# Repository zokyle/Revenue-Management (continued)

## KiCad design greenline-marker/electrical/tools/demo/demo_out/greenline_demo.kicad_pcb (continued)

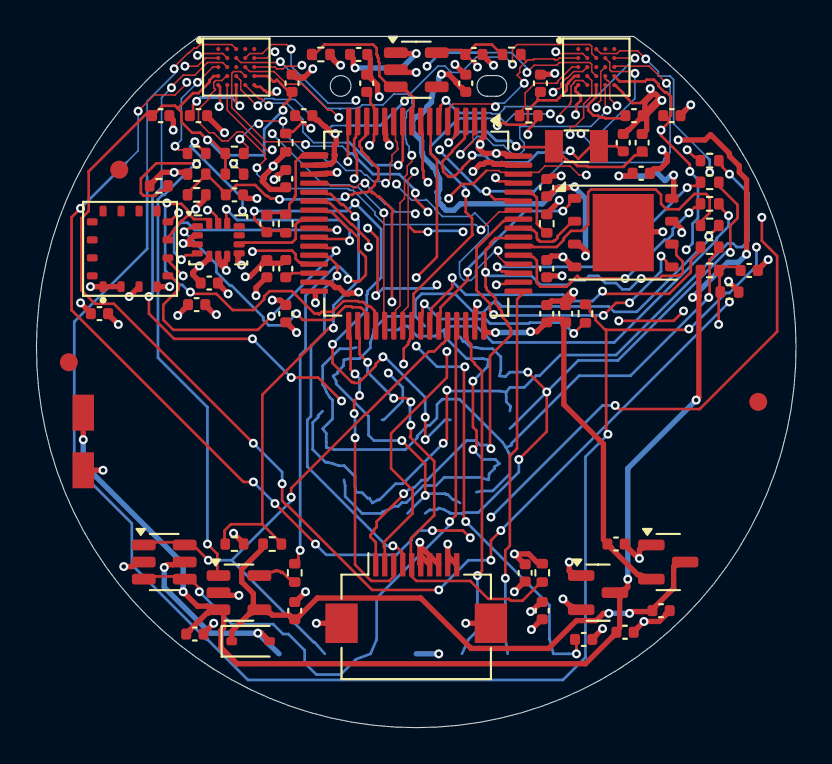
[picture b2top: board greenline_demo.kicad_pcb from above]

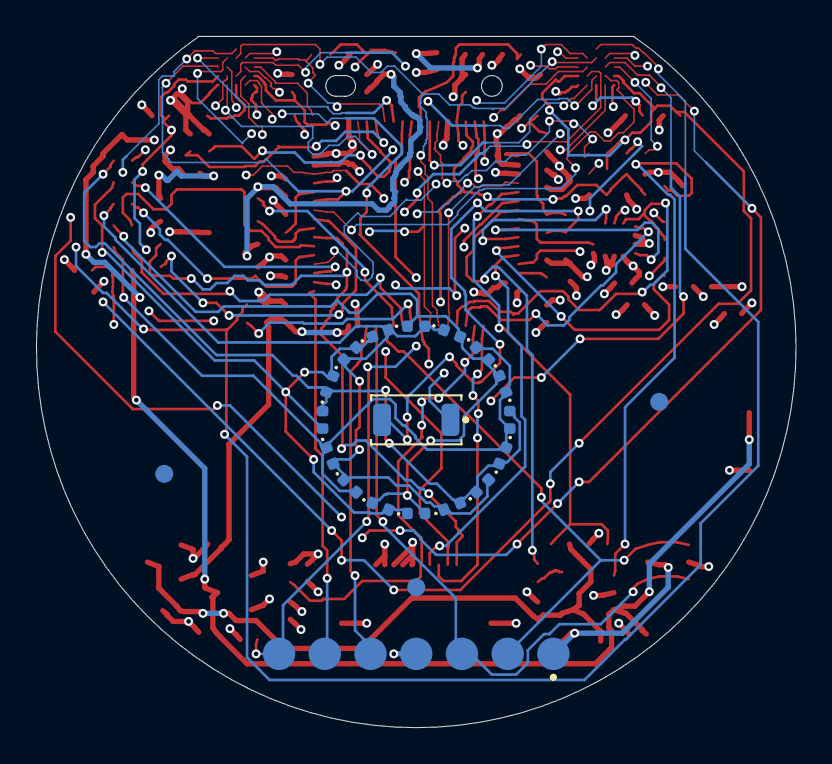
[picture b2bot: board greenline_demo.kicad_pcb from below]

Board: 4 copper layers, 42.2 x 38.4 mm, 101 parts (21 on the bottom side), 72 nets.

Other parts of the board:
FID1, FID2, FID3, FID4, FID5, FID6: Fiducial; Fiducial_1mm_Mask2mm
H1: NPTH 1.15mm; NPTH_1.15mm

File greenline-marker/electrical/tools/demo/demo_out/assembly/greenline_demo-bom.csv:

Item,Qty,References,Value,Description,Footprint,MPN,Manufacturer,Distributor,Distributor PN,Unit Price,Extended Price,DNP
1,17,C1 C2 C4 C5 C7 C10 C13 C14 C17 C18 C21 C22 C23 C24 C25 C27 C35,100n,MLCC 0402 100n,Capacitor_SMD:C_0402_1005Metric,GRM155R71C104KA88D,Murata,Digi-Key,490-3261-1-ND,0.0200,0.3400,
2,4,C3 C6 C29 C30,4u7,MLCC 0402 4u7,Capacitor_SMD:C_0402_1005Metric,GRM155R60J475ME47D,Murata,Digi-Key,490-5915-1-ND,0.0600,0.2400,
3,11,C8 C15 C16 C19 C20 C28 C31 C32 C33 C34 C36,1u,MLCC 0402 1u,Capacitor_SMD:C_0402_1005Metric,GRM155R61A105KE15D,Murata,Digi-Key,490-3890-1-ND,0.0300,0.3300,
4,1,C9,10n,MLCC 0402 10n,Capacitor_SMD:C_0402_1005Metric,GRM155R71H103KA88D,Murata,Digi-Key,490-1312-1-ND,0.0200,0.0200,
5,2,C11 C12,6p8,MLCC 0402 6p8,Capacitor_SMD:C_0402_1005Metric,GRM1555C1H6R8CA01D,Murata,Digi-Key,490-5947-1-ND,0.0300,0.0600,
6,1,C26,10p,MLCC 0402 10p,Capacitor_SMD:C_0402_1005Metric,GRM1555C1H100JA01D,Murata,Digi-Key,490-5921-1-ND,0.0300,0.0300,
7,8,D1 D3 D5 D7 D9 D11 D13 D15,LED red,grain LED 0402,LED_SMD:LED_0402_1005Metric,APHHS1005SURCK,Kingbright,Digi-Key,754-1104-1-ND,0.3500,2.8000,
8,8,D2 D4 D6 D8 D10 D12 D14 D16,LED NIR,grain LED 0402,LED_SMD:LED_0402_1005Metric,APHHS1005F3C,Kingbright,Digi-Key,754-1105-1-ND,0.3500,2.8000,
9,1,D17,Schottky,VBUS series Schottky,Diode_SMD:D_SOD-323,BAT60JFILM,STMicroelectronics,Digi-Key,497-3707-1-ND,0.3000,0.3000,
10,1,J1,LCD FPC 10,"LCD FPC connector, 10 x 0.5 mm",Connector_FFC-FPC:Hirose_FH12-10S-0.5SH_1x10-1MP_P0.50mm_Horizontal,FH12A-10S-0.5SH(55),Hirose,Digi-Key,HFJ110CT-ND,0.9000,0.9000,
11,1,PD1,Photodiode,photodiode (stand-in land pattern),gleda:Photodiode_4.8x2.5mm,VEMD5510C,Vishay,Digi-Key,VEMD5510CCT-ND,1.2000,1.2000,
12,5,R1 R2 R3 R4 R5,68R,Resistor 0402 1% 68R,Resistor_SMD:R_0402_1005Metric,RC0402FR-0768RL,Yageo,Digi-Key,RC0402FR-0768RL-ND,0.0100,0.0500,
13,1,R6,10R,Resistor 0402 1% 10R,Resistor_SMD:R_0402_1005Metric,RC0402FR-0710RL,Yageo,Digi-Key,RC0402FR-0710RL-ND,0.0100,0.0100,
14,1,R7,10k,Resistor 0402 1% 10k,Resistor_SMD:R_0402_1005Metric,RC0402FR-0710KL,Yageo,Digi-Key,RC0402FR-0710KL-ND,0.0100,0.0100,
15,3,R8 R9 R12,2k2,Resistor 0402 1% 2k2,Resistor_SMD:R_0402_1005Metric,RC0402FR-072K2L,Yageo,Digi-Key,RC0402FR-072K2L-ND,0.0100,0.0300,
16,3,R10 R11 R13,33R,Resistor 0402 1% 33R,Resistor_SMD:R_0402_1005Metric,RC0402FR-0733RL,Yageo,Digi-Key,RC0402FR-0733RL-ND,0.0100,0.0300,
17,7,R14 R17 R18 R19 R21 R22 R25,100k,Resistor 0402 1% 100k,Resistor_SMD:R_0402_1005Metric,RC0402FR-07100KL,Yageo,Digi-Key,RC0402FR-07100KL-ND,0.0100,0.0700,
18,1,R16,470k,Resistor 0402 1% 470k,Resistor_SMD:R_0402_1005Metric,RC0402FR-07470KL,Yageo,Digi-Key,RC0402FR-07470KL-ND,0.0100,0.0100,
19,1,R20,49k9,Resistor 0402 1% 49k9,Resistor_SMD:R_0402_1005Metric,RC0402FR-0749K9L,Yageo,Digi-Key,RC0402FR-0749K9L-ND,0.0100,0.0100,
20,2,R23 R24,1M,Resistor 0402 1% 1M,Resistor_SMD:R_0402_1005Metric,RC0402FR-071ML,Yageo,Digi-Key,RC0402FR-071ML-ND,0.0100,0.0200,
21,1,U1,STM32U585RIT6,"MCU, LQFP-64",Package_QFP:LQFP-64_10x10mm_P0.5mm,STM32U585RIT6,STMicroelectronics,Digi-Key,497-STM32U585RIT6-ND,9.5000,9.5000,
22,2,U2 U3,OVM7692,camera cube (stand-in ball map),gleda:CamCube_BGA25_P0.5,OVM7692-RYAA,OmniVision,Digi-Key,884-1027-1-ND,6.0000,12.0000,
23,1,U4,LSM6DSV16X,"6-axis IMU, LGA-14",Package_LGA:LGA-14_3x2.5mm_P0.5mm_LayoutBorder3x4y,LSM6DSV16XTR,STMicroelectronics,Digi-Key,497-LSM6DSV16XTRCT-ND,4.5000,4.5000,
24,1,U5,Inclinometer,"inclinometer, LGA-16 (stand-in pin map)",gleda:LGA-16_5x5mm_P1.0mm,IIS2ICLXTR,STMicroelectronics,Digi-Key,497-IIS2ICLXTRCT-ND,18.0000,18.0000,
25,1,U6,SPI flash,"SPI NOR flash 64 Mbit, WSON-8 6x5",Package_SON:WSON-8-1EP_6x5mm_P1.27mm_EP3.4x4.3mm,MX25R6435FZNIL0,Macronix,Digi-Key,1092-1187-1-ND,1.6000,1.6000,
26,1,U7,MCP1700-2.8,"LDO 2.8 V, always on",Package_TO_SOT_SMD:SOT-23,MCP1700T-2802E/TT,Microchip,Digi-Key,MCP1700T2802ETTCT-ND,0.4500,0.4500,
27,1,U8,LP5907-2.8,LDO 2.8 V for the cameras,Package_TO_SOT_SMD:SOT-23-5,LP5907MFX-2.8/NOPB,Texas Instruments,Digi-Key,296-38557-1-ND,0.6000,0.6000,
28,1,U9,MCP73831,Li-Po charger,Package_TO_SOT_SMD:SOT-23-5,MCP73831T-2ACI/OT,Microchip,Digi-Key,MCP73831T-2ACI/OTCT-ND,0.7000,0.7000,
29,1,U10,USBLC6-2SC6,USB ESD protection,Package_TO_SOT_SMD:SOT-23-6,USBLC6-2SC6,STMicroelectronics,Digi-Key,497-5235-1-ND,0.4000,0.4000,
30,1,U11,MCP1700-3.3,LDO 3.3 V for VDDUSB,Package_TO_SOT_SMD:SOT-23,MCP1700T-3302E/TT,Microchip,Digi-Key,MCP1700T3302ETTCT-ND,0.4500,0.4500,
31,1,Y1,32.768k,32.768 kHz crystal 3215,Crystal:Crystal_SMD_3215-2Pin_3.2x1.5mm,ABS07-120-32.768KHZ-T,Abracon,Digi-Key,535-11937-1-ND,0.6000,0.6000,

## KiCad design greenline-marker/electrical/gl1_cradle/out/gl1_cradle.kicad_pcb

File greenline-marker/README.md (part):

# GreenLine GL-1

Overview of the design package at revision E-EVT1 (revision E of the design, prepared for the first engineering test build; the words are explained below). Written 2026-11-20 for the owner of the project.

## 1. What this is, in five sentences

GreenLine GL-1 is the design of an electronic golf ball marker: a D-shaped puck 46.0 mm across and 7.6 mm thick that is set down behind the ball on a putting green.
It measures the direction and distance to the flagstick with two very small cameras, the tilt of the ground under it with an inertial sensor, and (as an experiment that ships switched off) the lean of the grass with a ring of small lights.
From those measurements it computes where to start the putt and draws that line on a round display on its top face, with the distance, the slope and the expected break.
It has no radio and no buttons; it is driven by placing, tapping and turning it, and it charges and exchanges data in a small cradle with a USB-C socket.
It is a practice and training device, and everything in this directory is a design on paper: no unit exists.

### Words used in this file

| Word | Meaning here |
|---|---|
| Revision E, E-EVT1 | The current issue of the design; the files also mention the earlier revisions C and D. EVT stands for engineering validation test: the first hand-built units, made to find out what is wrong. E-EVT1 is revision E as prepared for the first such build. |
| Specification | `design/DESIGN_SPEC.md`, the file that states what the product is and every design decision. |
| Amendment | A numbered change to the specification. Revision E has 36 of them, E1 to E36. |
| PROVISIONAL | The package's own mark for a value that was written down from memory or from a search extract and is not confirmed against the maker's document. |
| PROPOSED | A requirement or limit that is stated and that nobody has adopted or measured. |
| NOT MET | A requirement that the firmware model does not meet. A model result, not a measurement. |
| Gate | A question that must have a written answer before money is spent on something that cannot be undone. |
| Data sheet | The manufacturer's own document for a part. |
| Pin table, ball map | The table that says which pin of a chip carries which signal. Very small chips have solder balls underneath instead of pins; their table is called a ball map. |
| Stand-in | A plausible value or table put in so that the design could go on. It is not the maker's. |
| Routed board | A circuit board whose wiring (its copper tracks) has been drawn in full, so that fabrication files exist. "Changing the copper" means changing that wiring. |
| Design-rule check | An automatic check that the tracks of a board keep the widths and gaps the fabricator needs. |
| Firmware | The program that runs on the marker's processor. |
| Linked image | The one file that can be loaded into the processor. The firmware has been compiled (each source file checked and translated) but never linked into that file. |
| USB loader | A program that the processor's maker builds into the chip for loading new firmware over USB. |
| mrad | Milliradian: a slope or angle of 1 mm per metre, or 0.1 %. |

## 2. Status: read this before anything else

> **This is a design package. Nothing has been built.**
>
> - The package was produced entirely by software agents. No circuit board, printed part, fixture or marker has been fabricated, assembled, measured or run. The firmware has only ever run on a PC simulator.
> - No supplier has been asked for a quote and nothing has been ordered, certified or approved.
> - Every performance figure in this file is the output of a model or a simulation. None is a measurement.
> - [docs/RELEASE_GATES.md](docs/RELEASE_GATES.md) lists **104 open gates** between this package and the four orders that lead to a product (boards, enclosure and parts, building test units, selling). 32 of them are decisions that only the owner can take.
> - Several pin tables and part dimensions were written down from memory or from search extracts. The package marks them PROVISIONAL. The automatic checks compare the design with itself; they cannot tell whether a pin table copied from memory is the real one.

The request was for a "fully US-sourceable and ready to manufacture device". The package is not at that stage. The table says what "ready" covers today and what it does not.

| "Ready" does mean | "Ready" does not mean |
|---|---|
| The design is complete enough to review: specification, parameters, 3D models and drawings, two routed circuit boards with fabrication files, firmware that passes its tests on a PC, a simulation, and plans for sourcing, building and testing. | That boards or parts can be ordered today. 43 gates stand before the first board order alone. |
| The automatic checks of the package pass: the mechanical check report shows all checks passing, with 23 warnings and 8 recorded deviations from the specification, and the design-rule check of both boards shows 0 errors (`mechanical/export/check_report.md`; `electrical/README.md`, "Result"). | That the parts of the design agree with each other everywhere. The checks cover only what they compare. Known disagreements that no check covers: the cradle spring pin is drawn with a 0.635 mm tail in a 0.80 mm hole on the board and with a 0.76 mm tail in a 0.90 mm hole in the mechanical model (gate G-014); the files disagree on whether the two statement blocks of the legend hold 88 characters each or 88 together (G-045); `mechanical/README.md` gives the depth of the cradle pilot holes as 3 mm in one place and 3.2 mm in three others (G-107). Nor do the checks show that the design agrees with the real parts: that is what the PROVISIONAL items are about. |
| 64 of the 86 lines of the sourcing list are marked VERIFIED: 55 of the 72 purchased lines were seen listed by a US distributor or seller (42 with a stock figure), and for 9 of the 14 custom parts and outside services a US company was seen advertising that kind of work. No quote has been requested, and 17 purchased lines cannot be bought as they stand (`docs/SOURCING.md` sections 1.1 and 1.4). | That the device is US-made or "US-sourced". Where each part is made is unknown for almost every line, and the compliance checklist advises against the phrase in public (gates G-093 and G-097). |
| There is a written list of what must happen next, in order. | That the device works. Whether it reads a putt as well as the simulation says depends on inputs nobody has measured (section 6). |

The name for this stage is an EVT design package. EVT stands for engineering validation test: the first hand-built units, made to find out what is wrong.

This is a kitchen drawn on paper where the position of the sink was sketched from memory (the picture is from `docs/RELEASE_GATES.md`). The drawing is complete and consistent with itself, but the worktop must not be cut until someone has measured the real sink.

## 3. What it looks like

All six pictures are computer renders of the 3D model. Each carries the note "PROVISIONAL - not released" in its footer. They are not photographs.

*The assembled marker from the front and above. The flat face in front is the "visor", which points at the hole; the two small rectangles in it are the camera windows. The round glass on top covers the display, which is seen through a 22 mm opening. The small cross on the left of the top face is the vent with its drain grooves.*

*The underside. The plate is circuit-board material with a printed legend; the words "MAKER NAME" and "STATEMENTS RESERVED" are placeholders, because the regulatory text is not decided (gate G-085). The ring in the middle is the grain sensor: pairs of small lights round a light detector, sealed under clear resin. The slot at the bottom shows seven gold contact pads. The user's cradle touches four of them with spring pins (power, two data lines, ground); the other three are for the factory. The three small dots are steel or ceramic balls that stand 0.10 mm proud and act as feet on a hard surface.*

*Exploded view, with the labels of the render. The main parts, from top to bottom: cover glass, tape ring, the printed shell ("Tub"), the display ("Memory LCD"), a foam pad (the grey-purple rectangle), the battery ("LiPo cell"), the two camera cubes with their small fold prisms, the main circuit board ("Main PCB assembly"), an adhesive sheet, the baffle ring of the grain sensor (a black ring that keeps stray light from the light detector), and the base plate with its three ball feet. The small parts between them: two visor windows with their adhesive frames, the vent, two black hood gaskets, the adhesive frame and the flexible tail of the display, the battery leads, the black tape annulus under the baffle ring, the perimeter seal, the clear potting of the grain opening and the potting of the three balls. The round purple disc, second from the top, is an optional trial film (amendment E9) that is meant to keep the display readable through polarised sunglasses.*

*Cut-away. The stack at the centre, from the bottom: base plate, adhesive, circuit board, battery, foam, display glass, cover glass. On the right, one camera: the camera cube sits flat on the board and looks straight up, and a 2 mm prism on top of it turns its view forward through the visor window.*

*The marker in its charging and data cradle, seen from the rear right. The marker fits one way round only. A fixed lip holds its front edge and a sprung latch with a thumb tab holds the rear. The USB-C socket is in the rear face of the cradle.*

*Section through the marker in its cradle. A spring pin in the cradle presses up against a contact pad on the marker's underside; the lip and the latch hold the marker down against the pins. The floor of the cradle is drained.*

## 4. How it works

Each part is explained first with an everyday picture and then with the real mechanism and its numbers. Unless another file is named, the numbers come from `design/DESIGN_SPEC.md` (sections 2 to 6).

### 4.1 Two cameras: two eyes judging distance

**The picture.** Hold a finger at arm's length and look at it with one eye, then the other. The finger appears to jump sideways against the background. The closer the finger, the bigger the jump. Your brain uses that jump to judge distance. The marker does the same with two cameras a fixed distance apart, looking at the flagstick.

**The mechanism.**

- Two OmniVision OVM7692 camera cubes (each 2.95 x 3.47 x 2.76 mm) sit 20.0 mm apart. That spacing is the "baseline". The jump between the two images is called disparity and is measured in pixels. The focal length of the lens, expressed in pixels, is 657: an object 657 times as far away as it is wide covers one pixel.
- The cameras look out 5.6 mm above the turf. From that height the green is seen almost edge-on, so the cameras **cannot** map the surface between ball and hole: everything beyond a couple of metres collapses into one or two pixel rows. The specification says this plainly. What the cameras do deliver is the flagstick.
- From the flagstick they take three things: the direction to the hole (expected quality about 1 milliradian, which is 1 mm sideways per metre of distance), the distance, and the height of the lowest visible point of the stick, which tells whether the hole is above or below the ball.
- Two eyes 20 mm apart judge far distances poorly. For long putts the marker also uses the apparent height of the flagstick, which it learns per course. The simulated error of the combined distance (random part only) is 1 % at 1.5 m, 2 % at 3 m, 3.4 % at 6 m and 5 % at 12 m. The stick's top is only in view beyond about 6.6 m on a nominal unit and about 8.4 m on a worst-case one.
- The flagstick must be in the hole. Without it the golfer points the marker at the hole and dials in the distance, and the result is marked as approximate.
- PROVISIONAL: the pattern of solder balls under the camera and the lens data behind the field-of-view figures are not confirmed against the maker's documents. The camera pattern is the gravest single gate (G-001): if it is wrong, both camera areas of the board are redone.

### 4.2 The inertial sensor: a carpenter's level

**The picture.** A carpenter's level shows which way a surface tips by where the bubble goes. The marker carries an electronic version of that bubble. Lying on the green, it reads which way the ground under it falls and how steeply.

**The mechanism.**

- The part is an ST LSM6DSV16X, an inertial sensor that measures acceleration (and so the direction of gravity) and rotation. The firmware averages gravity for 1 second once the marker has lain still for 0.5 second.
- The sensor itself is expected to be good to about 0.5 milliradian. A milliradian (mrad) is a slope of 1 mm per metre, or 0.1 %.
- The weak point is not the sensor but how the puck sits on grass: the estimate is 2 to 5 mrad of error per placement, and **nobody has measured it**. The specification calls seating "the dominant error of the whole instrument". The simulation shows the tilt reading does nearly all the work for the aim line, so this unmeasured number decides how good the device is.
- A carpenter checks a level by turning it end for end. The marker uses the same trick twice: the Precision Read (read, spin the marker 180 degrees in place, read again) cancels the device's own bias, and the user zeroing routine on a hard flat surface works the same way.
- One reading tells the slope under the ball only. The slope along the rest of the putt can differ. Survey mode exists for that: two to four placements along the line.

### 4.3 The grain sensor: stroking velvet, with light

**The picture.** Stroke velvet one way and it looks light; stroke it the other way and it looks dark, because the fibres lean. Grass on a green leans too ("grain"), and a ball rolls differently with and against it. The grain sensor does not touch the grass. It shines small lights on it from different sides in turn and watches which side looks brightest.

**The mechanism.**

- On the underside, 16 small LEDs sit on a ring of 5.2 mm radius round one light detector (a photodiode): eight red and eight near-infrared, arranged as eight pairs at eight positions round the ring, 45 degrees apart (`design/master_params.yaml`, `grain_led_ring`). So the grass is lit from eight directions in two colours, which makes 16 separate lights.
- Each LED is switched on in turn and the detector reading is compared with the reading with the LED off. The research note's model puts the brightest direction on the side the blades lean away from (`docs/research/grain-sensing.md`).
- **This is the least proven part of the design.** The specification's own entry reads: "Unproven. Reviewer estimate 15-25 % chance the optical reading improves the line." The research note found that for a single reading the random noise is as large as the signal.
- For that reason the grain sensor ships disabled, and every accuracy figure in section 6 is without it.

### 4.4 The solver: rolling a virtual ball until it drops

**The picture.** Imagine a practice green inside the marker that matches what it just measured. The marker rolls a virtual ball on it, sees where the ball ends up, corrects the aim and the speed, and rolls again, until the ball goes through the hole at the wanted pace. The aim of that last roll is the line it draws.

**The mechanism.**

- From the tilt and the height of the hole the firmware fits a simple curved surface between ball and hole. The sources call it a "quadratic patch": a surface that can tilt and bend like a shallow dish or saddle, and cannot ripple. It then needs the green speed, which the golfer enters as a Stimp number (the usual measure of how fast a green is).
- The ball's motion is computed in small time steps: friction slows it, slope pulls it sideways. The target pace is a ball that would stop 0.30 m past the hole on a flat green (adjustable).
- It takes few rolls and many small steps. In the firmware's own bench table a typical Quick Read takes 5 trial rolls and about 730 time steps; over 240 simulated reads the most was 57 rolls and 25,144 steps (`firmware/README.md`, section "Solver"). The work is capped at 300,000 steps, about 1 to 2 seconds by the timing model.
- On very steep slopes no stable answer exists: near the slope on which a ball no longer stops, the review found the aim flipping on a one-microradian change of input. The marker then says "TOO STEEP" and draws only a dashed line, or no line (amendments E31 and E33).
- The firmware solver is a C port of the Python reference in `sim/`, and is tested against it on a PC.

### 4.5 The electronics as a block diagram

```mermaid
flowchart LR
    subgraph CRADLE["Cradle"]
        USBC["USB-C socket, 5 V"]
        PINS["4 spring pins in the user cradle (of 7 pads): power, 2 data, ground"]
        USBC --> PINS
    end

    subgraph POWER["Power"]
        SW["Ideal-diode switch"]
        CHG["Charger BQ25101, 19.8 mA"]
        CELL["Lithium-polymer cell, about 43 mAh listed"]
        REG["2.8 V regulator, always on"]
        CAMREG["2.8 V camera regulator, on only during a read"]
        SW --> CHG --> CELL
        CELL --> REG
        CELL --> CAMREG
    end

    subgraph BRAIN["Processor"]
        MCU["STM32U585 microcontroller"]
    end

    subgraph SENSE["Sensors"]
        CAML["Camera left"]
        CAMR["Camera right"]
        IMU["Inertial sensor: tilt, taps, turns"]
        GRAIN["Grain ring: 16 LEDs and 1 photodiode"]
    end

    DISP["Display, 128 x 128 points"]
    FLASH["Memory chip: settings, calibration, log"]

    PINS -->|"5 V"| SW
    PINS <-->|"USB data"| MCU
    REG --> MCU
    CAMREG --> CAML
    CAMREG --> CAMR
    CAML -->|"shared image bus"| MCU
    CAMR -->|"shared image bus"| MCU
    IMU <--> MCU
    GRAIN <--> MCU
    MCU --> DISP
    MCU <--> FLASH
```

What to notice in the diagram: power flows from the cradle on the left through the charger into the cell, and from the cell through two regulators to everything else; every sensor reports to the one processor; nothing leaves the marker except through the cradle pins.

Three terms in the boxes. The ideal-diode switch is an electronic one-way valve: it lets the cradle's 5 V in and lets nothing flow back out to the contact pads. A regulator turns the cell's changing voltage into a steady 2.8 V. The shared image bus is one set of data lines that both cameras use in turn, so the processor reads one camera at a time.

Points worth knowing, all from `design/DESIGN_SPEC.md` sections 3 and 4:

- There is one processor and no radio. Settings are made on the device; logs, calibration and firmware updates go through the cradle as an ordinary USB device.
- The cameras are powered only during a read, because they take most of the energy (92 % of the charge of a read in the model, `docs/POWER_BUDGET.md`).
- The charger has its own temperature sensor at the cell and stops charging outside its temperature window without any help from the firmware. Its temperature thresholds and its pin table are PROVISIONAL.
- The marker has seven contact pads. The user's cradle fits four spring pins. The factory version of the cradle fits all seven; the three extra pins give service access to the processor.

### 4.6 One read, step by step

```mermaid
sequenceDiagram
    participant G as Golfer
    participant M as Marker (processor)
    participant I as Inertial sensor
    participant C as Two cameras
    participant D as Display

    G->>M: Place the marker behind the ball, visor toward the hole
    I->>M: Motion wakes the marker
    I->>M: Still for 0.5 s (settle)
    I->>M: Gravity averaged for 1 s (tilt)
    M->>C: Camera power on
    C->>M: Image strips, left right right left, repeated
    M->>C: Camera power off after 2.2 to 2.8 s
    M->>M: Find the flagstick, combine the two distance estimates, fit the surface, solve the putt
    M->>D: Draw the line, distance, slope, break, confidence
    D->>G: Result 4.15 to 4.84 s after the marker came to rest
    Note over M,D: The result stays for 45 s, then the marker sleeps
```

The times are from the firmware's timing model in the current test log (`firmware/build/readme/test.log`): 4.45 s at the nominal setting, 4.15 to 4.84 s over the estimated range. Amendment E15 of the specification still says "4.1 to 4.8 s", from an earlier run of the model. The times are not measured, and the model rests on an estimated factor between PC and processor speed (gate G-077).

## 5. Key numbers

| Item | Value | Standing | Source |
|---|---|---|---|
| Marker size | 46.0 mm across, 7.6 mm thick, D-shaped | Design value | `design/DESIGN_SPEC.md` section 1 |
| Marker mass | 12.11 g | Estimate from the 3D model with typical densities, no solder | `mechanical/README.md` section 2 |
| Cradle | 60 x 60 mm, 22.6 mm high overall; about 30.4 g for the factory version with all seven pins (the user cradle has four) | Design value; mass estimated | `design/DESIGN_SPEC.md` section 5; `mechanical/README.md` section 2 |
| Cell | Lithium-polymer, 2 x 10 x 30 mm, about 43 mAh. With its protection board it is modelled as 34 x 10 x 2 mm, which is the size on the label in the exploded view | Listing only; capacity, protection-board length (PROVISIONAL) and safety certificates not obtained. The research notes suspect 34 mAh | `design/DESIGN_SPEC.md` section 3; `mechanical/README.md` part list item 4; `docs/POWER_BUDGET.md` section 1 |
| Charging | 19.8 mA in the cradle; at least 2.2 h from empty | Model; no model of a whole charge exists | `docs/POWER_BUDGET.md` section 2 |
| Read time | Result 4.15 to 4.84 s after the marker comes to rest (4.45 s nominal); cameras on for 2.16 to 2.76 s | MODEL, not measured. The specification (E15) still says 4.1 to 4.8 s | `firmware/build/readme/test.log`; `firmware/README.md` "End to end" |
| Reads per charge | 594 read cycles to empty (528 to 658) | MODEL on the listed capacity | `docs/POWER_BUDGET.md` section 3 |
| Standby | 76 days asleep to empty, underside dark (23.68 microamps) | MODEL | `docs/POWER_BUDGET.md` sections 2 and 3 |
| Ship mode (the lowest power state, for the weeks in a box) | 12.93 microamps against a requirement of at most 5 | **NOT MET** in the model; needs a hardware change or a changed requirement. The specification and the YAML still say ship mode is not modelled (gate G-107) | `docs/POWER_BUDGET.md` section 4 |
| Display | Sharp memory LCD, 128 x 128 points, seen through a 22 mm round opening | Part chosen; tail geometry and pin order PROVISIONAL | `design/DESIGN_SPEC.md` sections 3 and 4 |
| Cameras | Two, 20.0 mm apart, focal length 657 pixels, optical axis 5.6 mm above the turf | Design values; ball pattern and lens data PROVISIONAL | `design/DESIGN_SPEC.md` sections 2 and 5 |
| Main board | 4 layers, 0.8 mm thick, D-shaped | Routed; design-rule check passes; not ordered | `design/DESIGN_SPEC.md` section 4; `electrical/README.md` |
| Cradle board | 2 layers, 1.0 mm thick | Routed; not ordered | `design/DESIGN_SPEC.md` E36 |
| Open gates | 104 (43 + 20 + 22 + 19), of them 32 owner decisions | Count on 2026-11-20, after three gates closed and five were added that day | `docs/RELEASE_GATES.md` sections 1 and 10 |

## 6. How accurate would it be? What the simulation says, and what it does not

The package contains a simulation (`sim/`). It builds synthetic greens on a computer, simulates what the marker's sensors would report on them, runs the same estimator the firmware uses, and then rolls the ball along the line the marker would show. Doing this for many random cases is called a Monte Carlo run.

**What the run covers** (`sim/results/REPORT.md`): 3600 putts, at six lengths from 1.5 to 12 m, on four classes of synthetic green, 150 greens per class and length. Seating error of the puck assumed 2.5 mrad. Grain sensor off. The table below is for a perfect stroke along the displayed line, all lengths pooled.

| Method | Putts holed | Holed at 3 m | Holed at 6 m | Median sideways miss |
|---|---|---|---|---|
| No read: aim straight at the flag | 8.9 % | 11 % | 4 % | 23.2 cm |
| Quick Read (one placement) | 29.5 % | 44 % | 13 % | 9.9 cm |
| Precision Read (read, spin, read) | 31.6 % | 48 % | 14 % | 8.6 cm |
| Survey, three placements | 34.4 % | 52 % | 23 % | 7.1 cm |
| A golfer who reads cross slope to 0.5 % | 29.5 % | 42 % | 14 % | 9.5 cm |
| A golfer who reads cross slope to 1 % | 19.3 % | 25 % | 7 % | 16.4 cm |

Source: `sim/results/REPORT.md` section 1.

In words: in the simulation a Quick Read is about level with a golfer who reads slope very well, and clearly ahead of one who reads it moderately well. With human stroke error added (1 degree in direction, 6 % in speed, which the report calls an elite level) the Quick Read holes 21.0 % and even a perfect read holes only 32.7 %.

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
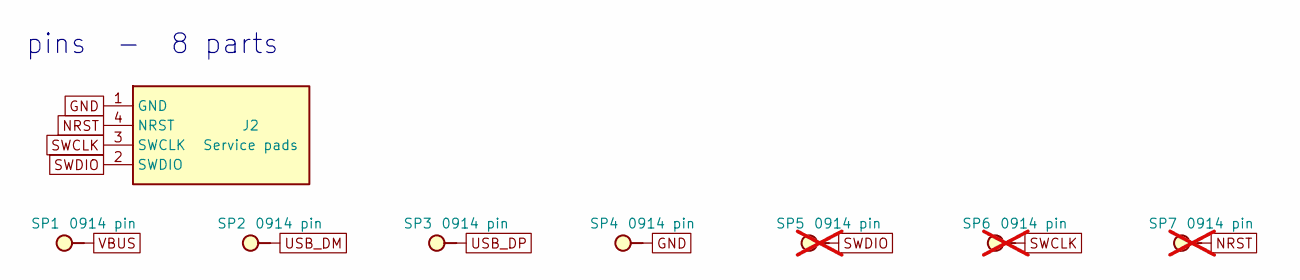
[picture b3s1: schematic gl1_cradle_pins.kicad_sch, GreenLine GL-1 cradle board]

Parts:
J2: Service pads; ServicePads_4x1.5mm_P2.54
SP1, SP2, SP3, SP4: 0914 pin; MillMax_0914_TH_PROVISIONAL; MPN 0914-0-15-20-77-14-11-0
SP5, SP6, SP7: 0914 pin; MillMax_0914_TH_PROVISIONAL; MPN 0914-0-15-20-77-14-11-0; not fitted

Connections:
GND: J2.1 (GND), SP4.1; also elsewhere on the board
NRST: J2.4 (NRST), SP7.1
SWCLK: J2.3 (SWCLK), SP6.1
SWDIO: J2.2 (SWDIO), SP5.1
USB_DM: SP2.1; also elsewhere on the board
USB_DP: SP3.1; also elsewhere on the board
VBUS: SP1.1; also elsewhere on the board

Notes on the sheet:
pins - 8 parts

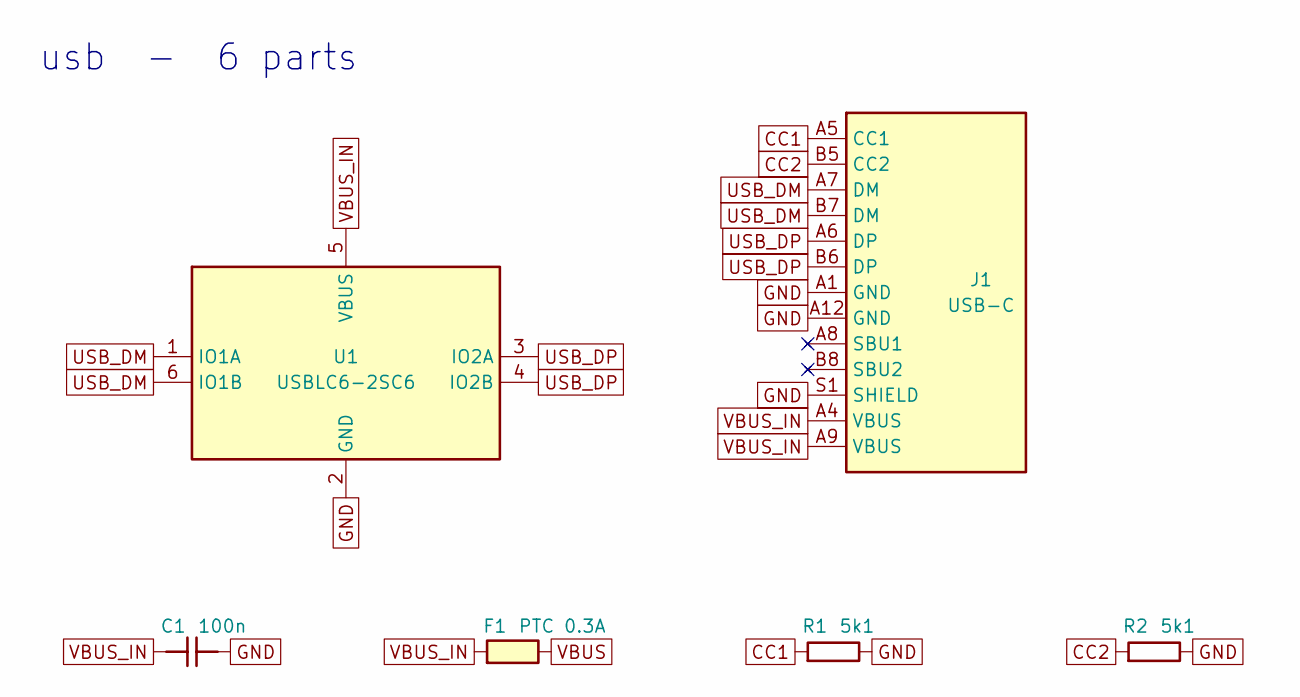
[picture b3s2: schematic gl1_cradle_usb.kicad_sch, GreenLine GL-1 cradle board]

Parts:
C1: 100n; C_0402_1005Metric; MPN GRM155R71C104KA88D
F1: PTC 0.3A; Fuse_0603_1608Metric; MPN MF-FSMF035X-2
J1: USB-C; USB_C_Receptacle_GCT_USB4105-xx-A_16P_TopMnt_Horizontal_GL1; MPN USB4105-GF-A
R1, R2: 5k1; R_0402_1005Metric; MPN RC0402FR-075K1L
U1: USBLC6-2SC6; SOT-23-6; MPN USBLC6-2SC6

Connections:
CC1: J1.A5 (CC1), R1.1
CC2: J1.B5 (CC2), R2.1
GND: C1.2, J1.A1 (GND), J1.A12 (GND), J1.S1 (SHIELD), R1.2, R2.2, U1.2 (GND); also elsewhere on the board
USB_DM: J1.A7 (DM), J1.B7 (DM), U1.1 (IO1A), U1.6 (IO1B); also elsewhere on the board
USB_DP: J1.A6 (DP), J1.B6 (DP), U1.3 (IO2A), U1.4 (IO2B); also elsewhere on the board
VBUS: F1.2; also elsewhere on the board
VBUS_IN: C1.1, F1.1, J1.A4 (VBUS), J1.A9 (VBUS), U1.5 (VBUS)

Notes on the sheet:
usb - 6 parts

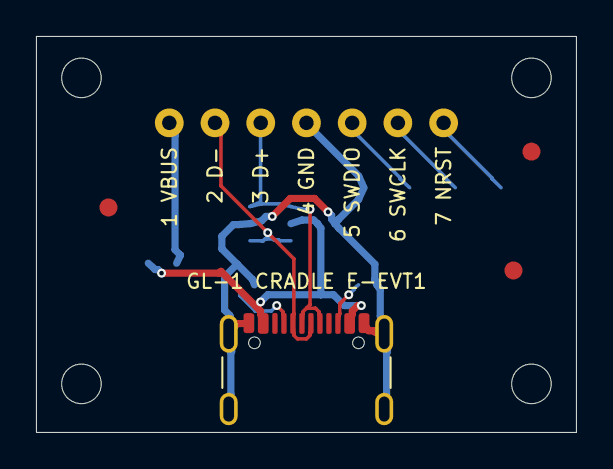
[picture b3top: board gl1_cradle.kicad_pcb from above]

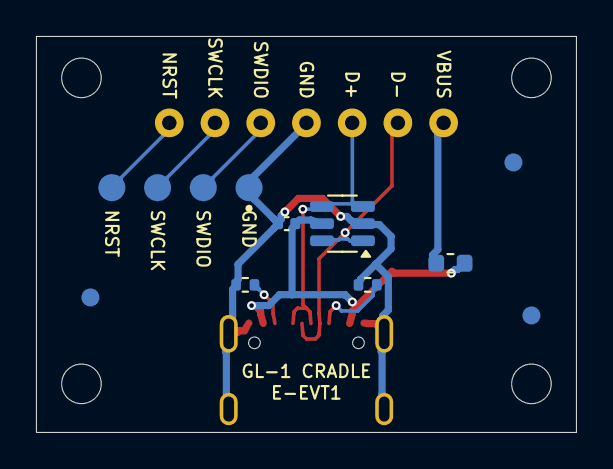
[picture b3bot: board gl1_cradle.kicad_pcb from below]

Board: 2 copper layers, 30.0 x 22.0 mm, 24 parts (9 on the bottom side), 10 nets.

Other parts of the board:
FID1, FID2, FID3, FID4, FID5, FID6: Fiducial; Fiducial_1mm_Mask2mm
MH1, MH2, MH3, MH4: NPTH 2.2mm; NPTH_2.2mm

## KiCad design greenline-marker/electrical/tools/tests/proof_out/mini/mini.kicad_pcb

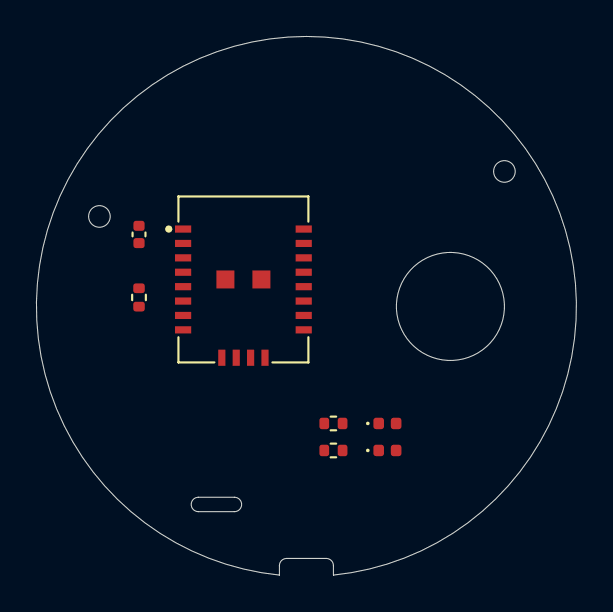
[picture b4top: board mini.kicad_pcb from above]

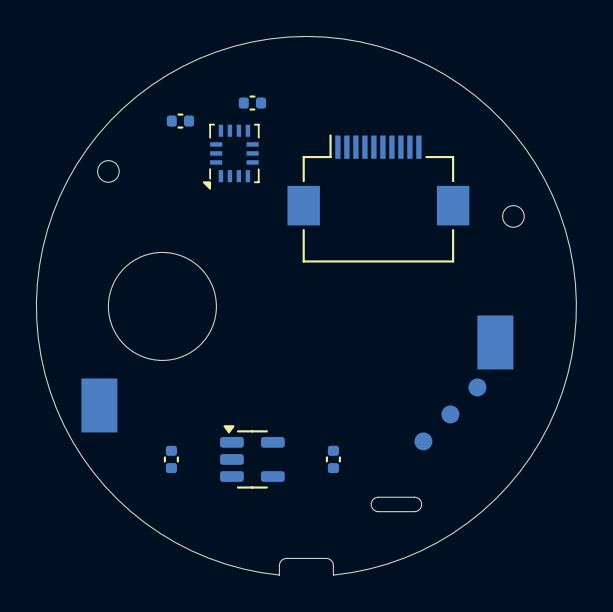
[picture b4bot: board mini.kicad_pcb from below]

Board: 4 copper layers, 30.0 x 29.9 mm, 21 parts (12 on the bottom side), 19 nets, no tracks yet.

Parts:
BT1: BAT+; BatteryTab_2x3mm
BT2: BAT-; BatteryTab_2x3mm
C1, C3, C4: 1u; C_0402_1005Metric
C2, C5: 100n; C_0402_1005Metric
D1, D2: LED; LED_0402_1005Metric
H1, H2: NPTH 1.2mm; NPTH_1.2mm
J1: FPC 10; Hirose_FH12-10S-0.5SH_1x10-1MP_P0.50mm_Horizontal
R1, R2: 1k; R_0402_1005Metric
R3: 10k; R_0402_1005Metric
TP1, TP2, TP3: TP; TestPad_D1mm
U1: MiniModule; MiniModule_7x9
U2: BMI270; Bosch_LGA-14_3x2.5mm_P0.5mm
U3: LDO 3V0; SOT-23-5

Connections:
+3V0: C1.1, C2.1, C4.1, C5.1, J1.2, R3.1, U1.2 (VDD), U2.5 (VDDIO), U2.8 (VDD), U3.5 (VOUT)
CAM_EN: J1.10, R3.2, U1.18 (EN)
D0: J1.6, U1.9 (D0)
D1: J1.7, U1.10 (D1)
D2: J1.8, U1.11 (D2)
D3: J1.9, U1.12 (D3)
GND: BT2.1, C1.2, C2.2, C3.2, C4.2, C5.2, D1.1 (K), D2.1 (K), J1.1, J1.MP, TP3.1, U1.1 (GND), U1.8 (GND), U1.13 (GND), U1.20 (GND), U1.21 (GND), U2.6 (GNDIO), U2.7 (GND), U3.2 (GND)
IMU_CS: U1.6 (CS), U2.12 (CSB)
IMU_INT: U1.7 (INT), U2.4 (INT1)
LED1: R1.1, U1.14 (LED1)
LED1_A: D1.2 (A), R1.2
LED2: R2.1, U1.15 (LED2)
LED2_A: D2.2 (A), R2.2
MISO: J1.5, U1.5 (MISO), U2.1 (SDO)
MOSI: J1.4, U1.4 (MOSI), U2.14 (SDX)
SCK: J1.3, U1.3 (SCK), U2.13 (SCX)
SWCLK: TP2.1, U1.17 (SWCLK)
SWDIO: TP1.1, U1.16 (SWDIO)
VBAT: BT1.1, C3.1, U3.1 (VIN), U3.3 (EN)

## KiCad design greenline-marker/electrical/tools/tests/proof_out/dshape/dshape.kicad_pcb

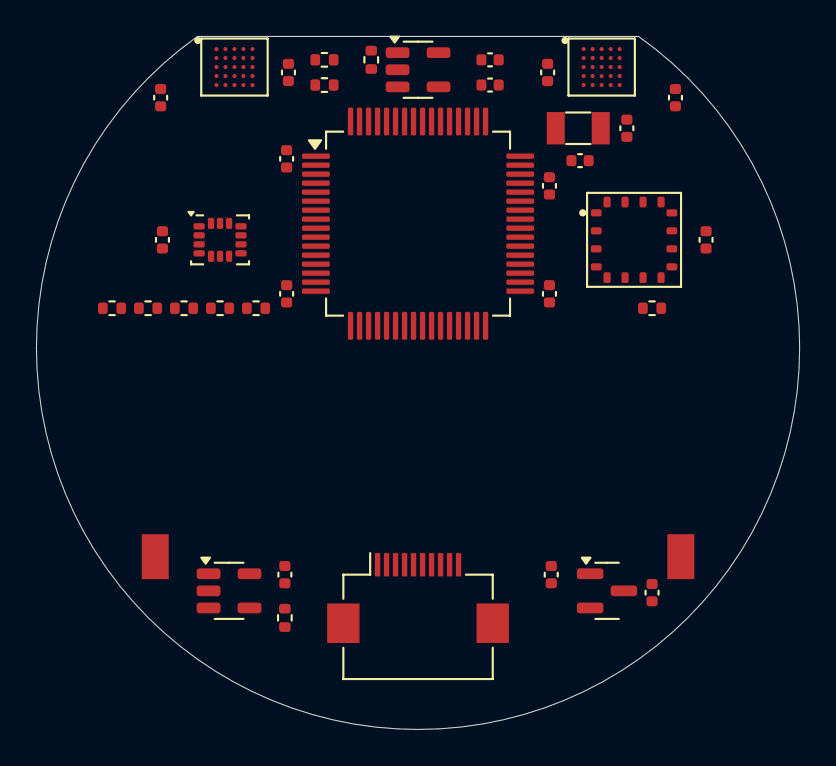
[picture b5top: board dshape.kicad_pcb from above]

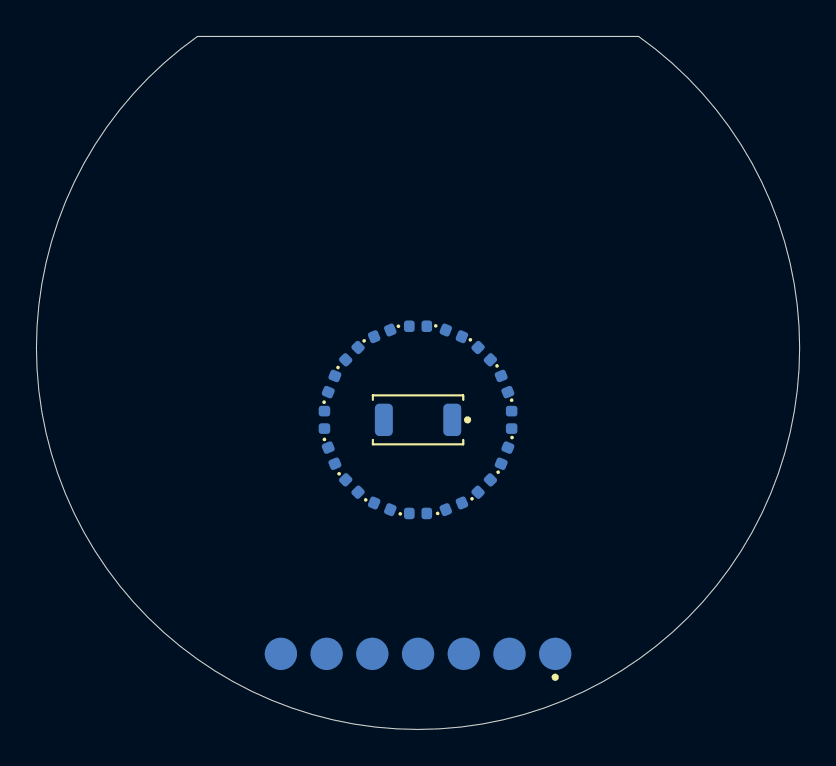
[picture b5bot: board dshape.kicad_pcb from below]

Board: 4 copper layers, 42.4 x 38.5 mm, 57 parts (18 on the bottom side), 56 nets, no tracks yet.

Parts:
BT1: BAT+; BatteryTab_1.5x2.5mm
BT2: BAT-; BatteryTab_1.5x2.5mm
C1, C2, C3, C12, C13, C16, C17: 100n; C_0402_1005Metric
C4: 4u7; C_0402_1005Metric
C5, C6, C7, C8, C9, C10, C11: 1u; C_0402_1005Metric
C14, C15: 12p; C_0402_1005Metric
D1, D3, D5, D7, D9, D11, D13, D15: LED red; LED_0402_1005Metric
D2, D4, D6, D8, D10, D12, D14, D16: LED NIR; LED_0402_1005Metric
J1: LCD FPC 10; Hirose_FH12-10S-0.5SH_1x10-1MP_P0.50mm_Horizontal
J2: Cradle pads; ContactRow_7x1.8mm_P2.54
PD1: Photodiode; Photodiode_4.8x2.5mm
R1, R2, R3, R4, R5: 68R; R_0402_1005Metric
R6, R7, R10: 2k2; R_0402_1005Metric
R8: 49k9; R_0402_1005Metric
R9: 100k; R_0402_1005Metric
U1: MCU LQFP-64; LQFP-64_10x10mm_P0.5mm
U2, U3: Camera cube; CamCube_BGA25_P0.5
U4: IMU LGA-14; LGA-14_3x2.5mm_P0.5mm_LayoutBorder3x4y
U5: Inclinometer LGA-16; LGA-16_5x5mm_P1.0mm
U7: LDO 3V0; SOT-23
U8: LDO 2V8; SOT-23-5
U9: Charger; SOT-23-5
Y1: 32.768k; Crystal_SMD_3215-2Pin_3.2x1.5mm

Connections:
+3V0: C1.1, C2.1, C3.1, C4.1, C11.1, C12.1, C13.1, J1.6, J1.7, J1.8, U1.1 (VDD), U1.19 (VDD), U1.32 (VDD), U1.48 (VDD), U1.64 (VDD), U4.5 (VDDIO), U4.8 (VDD), U5.1 (VDD), U5.2 (VDDIO), U7.2 (VOUT)
CAM_D0: U1.50 (D0), U2.B2 (D0), U3.B2 (D0)
CAM_D1: U1.51 (D1), U2.B3 (D1), U3.B3 (D1)
CAM_D2: U1.52 (D2), U2.B4 (D2), U3.B4 (D2)
CAM_D3: U1.53 (D3), U2.C2 (D3), U3.C2 (D3)
CAM_D4: U1.54 (D4), U2.C3 (D4), U3.C3 (D4)
CAM_D5: U1.55 (D5), U2.C4 (D5), U3.C4 (D5)
CAM_D6: U1.56 (D6), U2.D2 (D6), U3.D2 (D6)
CAM_D7: U1.57 (D7), U2.D3 (D7), U3.D3 (D7)
CAM_EN: R9.1, U1.44 (CAM_EN), U8.3 (EN)
CAM_HREF: U1.59 (HREF), U2.D4 (HREF), U3.D4 (HREF)
CAM_L_DVDD: C7.1, U2.D5 (DVDD)
CAM_PCLK: U1.58 (PCLK), U2.A2 (PCLK), U3.A2 (PCLK)
CAM_PWDN_L: U1.46 (PWDN_L), U2.C1 (PWDN)
CAM_PWDN_R: U1.45 (PWDN_R), U3.C1 (PWDN)
CAM_R_DVDD: C8.1, U3.D5 (DVDD)
CAM_SCL_L: R6.2, U1.62 (SCL_L), U2.B1 (SCL)
CAM_SCL_R: R7.2, U1.33 (SCL_R), U3.B1 (SCL)
CAM_SDA: R10.2, U1.49 (SDA), U2.B5 (SDA), U3.B5 (SDA)
CAM_VSYNC: U1.60 (VSYNC), U2.A3 (VSYNC), U3.A3 (VSYNC)
CAM_XVCLK: U1.61 (XVCLK), U2.A4 (XVCLK), U3.A4 (XVCLK)
CHG_PROG: R8.1, U9.5 (PROG)
CHG_STAT: U1.40 (CHG_STAT), U9.1 (STAT)
CP1: D1.2 (A), D2.1 (K), D9.1 (K), D10.2 (A), D11.2 (A), D12.1 (K), R1.2
CP1_MCU: R1.1, U1.25 (CP1)
CP2: D1.1 (K), D2.2 (A), D3.2 (A), D4.1 (K), D13.2 (A), D14.1 (K), R2.2
CP2_MCU: R2.1, U1.26 (CP2)
CP3: D3.1 (K), D4.2 (A), D5.2 (A), D6.1 (K), D11.1 (K), D12.2 (A), D15.2 (A), D16.1 (K), R3.2
CP3_MCU: R3.1, U1.27 (CP3)
CP4: D5.1 (K), D6.2 (A), D7.2 (A), D8.1 (K), D13.1 (K), D14.2 (A), R4.2
CP4_MCU: R4.1, U1.28 (CP4)
CP5: D7.1 (K), D8.2 (A), D9.2 (A), D10.1 (K), D15.1 (K), D16.2 (A), R5.2
CP5_MCU: R5.1, U1.29 (CP5)
CS_IMU: U1.5 (CS_IMU), U4.12 (CS)
CS_INC: U1.6 (CS_INC), U5.5 (CS)
GND: BT2.1, C1.2, C2.2, C3.2, C4.2, C5.2, C6.2, C7.2, C8.2, C9.2, C10.2, C11.2, C12.2, C13.2, C14.2, C15.2, C16.2, C17.2, J1.9, J1.10, J1.MP, J2.4, PD1.A, R8.2, R9.2, U1.18 (VSS), U1.31 (VSS), U1.47 (VSS), U1.63 (VSS), U2.E2 (GND1), U2.E3 (GND2), U2.E4 (GND3), U3.E2 (GND1), U3.E3 (GND2), U3.E4 (GND3), U4.2 (SDX), U4.3 (SCX), U4.6 (GND1), U4.7 (GND2), U5.3 (GND1), U5.4 (GND2), U7.1 (GND), U8.2 (GND), U9.2 (VSS)
IMU_INT: U1.7 (IMU_INT), U4.4 (INT1)
LCD_DISP: J1.5, U1.24 (LCD_DISP)
LCD_EXTCOMIN: J1.4, U1.23 (LCD_EXTCOMIN)
LCD_SCLK: J1.1, U1.20 (LCD_SCLK)
LCD_SCS: J1.3, U1.22 (LCD_SCS)
LCD_SI: J1.2, U1.21 (LCD_SI)
NRST: J2.7, U1.36 (NRST)
OSC32_IN: C14.1, U1.8 (OSC32_IN), Y1.1
OSC32_OUT: C15.1, U1.9 (OSC32_OUT), Y1.2
PD_K: PD1.K, U1.30 (PD_IN)
SPI_MISO: U1.4 (SPI_MISO), U4.1 (SDO), U5.8 (MISO)
SPI_MOSI: U1.3 (SPI_MOSI), U4.14 (SDA), U5.7 (MOSI)
SPI_SCK: U1.2 (SPI_SCK), U4.13 (SCL), U5.6 (SCK)
SWCLK: J2.6, U1.35 (SWCLK)
SWDIO: J2.5, U1.34 (SWDIO)
USB_DM: J2.2, U1.37 (USB_DM)
USB_DP: J2.3, U1.38 (USB_DP)
V2V8_CAM: C6.1, C16.1, C17.1, R6.1, R7.1, R10.1, U2.C5 (AVDD), U2.D1 (DOVDD), U3.C5 (AVDD), U3.D1 (DOVDD), U8.5 (VOUT)
VBAT: BT1.1, C5.1, C10.1, U7.3 (VIN), U8.1 (VIN), U9.3 (VBAT)
VBUS: C9.1, J2.1, U1.39 (VBUS_SENSE), U9.4 (VDD)

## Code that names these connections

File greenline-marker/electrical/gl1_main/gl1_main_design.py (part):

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LM66100_HEIGHT = 1.1           # PROVISIONAL (SC-70 maximum, memory)

#: PROVISIONAL - every number behind the supply-chain table of NETLIST_NOTES 4.1
#: (cradle USB connector -> fuse -> spring pins -> ideal-diode switch U12 (E25) -> VBUS_D).
#: None of them was read from a data sheet.  ``charger_vin_min`` is the figure
#: docs/research/power.md records for the BQ2510x ("4.45-6.45 V operating
#: input", marked UNVERIFIED there); what the charger does below it (input
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#: STM32U585RITx in LQFP-64, pad 1 .. 64 (PINDATA; check_pinmap.py compares
#: every row with ST's STM32U585RITx.xml and with the installed KiCad symbol).
MCU_PAD_NAMES = (
    "VBAT PC13 PC14 PC15 PH0 PH1 NRST PC0 PC1 PC2 PC3 VSSA VDDA PA0 PA1 PA2 "
    "PA3 VSS VDD PA4 PA5 PA6 PA7 PC4 PC5 PB0 PB1 PB2 PB10 VCAP VSS VDD "
    "PB12 PB13 PB14 PB15 PC6 PC7 PC8 PC9 PA8 PA9 PA10 PA11 PA12 PA13 VSS VDDUSB "
    "PA14 PA15 PC10 PC11 PC12 PD2 PB3 PB4 PB5 PB6 PB7 PH3 PB8 PB9 VSS VDD").split()
assert len(MCU_PAD_NAMES) == 64


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#:   gl_pins.h), CHANGED (moved from the pin in ``was``; ``reason`` says why)
PINMAP = [
    # ---- camera port: fixed by the DCMI alternate functions (spec, PINDATA) --------------
    ("CAM_D0", "PC6", "CAM_D0", "AF", "DCMI_D0", 10, "none", CAM_OFF, S, None, ""),
    ("CAM_D1", "PC7", "CAM_D1", "AF", "DCMI_D1", 10, "none", CAM_OFF, S, None, ""),
    ("CAM_D2", "PC8", "CAM_D2", "AF", "DCMI_D2", 10, "none", CAM_OFF, S, None, ""),
    ("CAM_D3", "PC9", "CAM_D3", "AF", "DCMI_D3", 4, "none", CAM_OFF, S, None, ""),
    ("CAM_D4", "PC11", "CAM_D4", "AF", "DCMI_D4", 10, "none", CAM_OFF, S, None, ""),
    ("CAM_D5", "PB6", "CAM_D5", "AF", "DCMI_D5", 10, "none", CAM_OFF, S, None, ""),
    ("CAM_D6", "PB8", "CAM_D6", "AF", "DCMI_D6", 10, "none", CAM_OFF, S, None, ""),
    ("CAM_D7", "PB9", "CAM_D7", "AF", "DCMI_D7", 10, "none", CAM_OFF, S, None, ""),
    ("CAM_PIXCLK", "PA6", "CAM_PCLK", "AF", "DCMI_PIXCLK", 4, "none", CAM_OFF, S, None, ""),
    ("CAM_HREF", "PA4", "CAM_HREF", "AF", "DCMI_HSYNC", 10, "none", CAM_OFF, S, None, ""),
    ("CAM_VSYNC", "PB7", "CAM_VSYNC", "AF", "DCMI_VSYNC", 10, "none", CAM_OFF, S, None, ""),
    ("CAM_XVCLK", "PA8", "MCO", "AF", "RCC_MCO", 0, "none", CAM_OFF, S, None, ""),
    # ---- camera control: on the package edge that faces the cameras (pads 1-16) ----------
    ("CAM_L_SCL", "PC3", "CAM_SCL_L", "SCCB_OD", "GPIO", None, "none / 2k2 to V2V8_CAM", CAM_OFF, C, "PB3",
     "PB3 is needed for SPI1_SCK next to the flash; PC3 is the left end of the camera-facing edge"),
    ("CAM_L_PWDN", "PC2", "CAM_L_PWDN_MCU", "OUT_PP", "GPIO", None, "none / 1k series", CAM_OFF, C, "PH0",
     "PC2 sits next to CAM_L_SCL on the camera-facing edge; PH0 takes CAM_PWR_EN"),
    ("CAM_SCCB_SDA", "PC1", "CAM_SDA", "SCCB_OD", "GPIO", None, "none / 2k2 to V2V8_CAM", CAM_OFF, C, "PB5",
     "PB5 is needed for SPI1_MOSI next to the flash; PC1 is in the middle of the camera-facing edge"),
    ("CAM_R_SCL", "PC0", "CAM_SCL_R", "SCCB_OD", "GPIO", None, "none / 2k2 to V2V8_CAM", CAM_OFF, C, "PA10",
     "PA10 is on the battery-facing edge; PC0 faces the cameras, PA10 takes FLASH_CS"),
    ("CAM_R_PWDN", "PH3", "CAM_R_PWDN_MCU", "OUT_PP", "GPIO", None, "none / 10k to GND (BOOT0), 1k series", CAM_OFF, C, "PC12",
     "the BOOT0 pad must carry one signal (51 signals, 51 I/O pads). PWDN of the right camera suits it: the pad is "
     "on the edge next to that camera, the net has no pull-up (BOOT0 stays low at every reset) and a static output "
     "does not mind the 10k; the firmware's proposal, NTC_BIAS, would be loaded by it"),
    ("CAM_PWR_EN", "PH0", "CAM_EN", "OUT_PP", "GPIO", None, "none / 100k to GND", "low (rail off)", C, "PD2",
     "camera-facing edge; a static signal is the right neighbour for OSC32_OUT (pad 4); PD2 goes to the grain LEDs"),
    # ---- LCD (J1): pads 28, 29, 33 are the lower left corner, the way down to J1 -----------
    ("LCD_SCS", "PB10", "LCD_SCS", "OUT_PP", "GPIO", None, "none / 100k to GND", "low (not selected)", P, None, ""),
    ("LCD_DISP", "PB12", "LCD_DISP", "OUT_PP", "GPIO", None, "none / 100k to GND (and 200k: grain bias divider)",
     "low (display off)", C, "PB1",
     "exchanged with IMU_CS (see there): a line with a pull-DOWN is what the ROM bootloader's SPI2 chip-select "
     "input can carry without harm; pad 33 is on the way down to J1"),
    ("LCD_EXTCOMIN", "PB2", "LCD_EXTCOMIN", "AF", "LPTIM1_CH1", 1, "none", "low until LPTIM1 runs", S, None, ""),
    # ---- SPI1: flash and LCD.  MISO is fixed on PB4, so clock and data sit on its neighbours
    ("SPI1_SCK", "PB3", "SPI1_SCK", "AF", "SPI1_SCK", 5, "none", "low", C, "PA5",
     "PB3 / PB4 / PB5 are three adjacent pads on the edge that faces the flash; PA5 is on the opposite edge"),
    ("SPI1_MISO", "PB4", "SPI1_MISO", "AF", "SPI1_MISO", 5, "none", "input", S, None, ""),
    ("SPI1_MOSI", "PB5", "SPI1_MOSI", "AF", "SPI1_MOSI", 5, "none", "low", C, "PA7",
     "see SPI1_SCK"),
    ("FLASH_CS", "PA10", "FLASH_CS", "OUT_PP", "GPIO", None, "none / 100k to V2V8", "high (not selected)", C, "PA15",
     "PA10 is the ROM bootloader's USART1_RX: a pulled-up chip select is exactly the idle level it wants there, "
     "a floating charlieplex line is not. PA15 is no place for a chip select either: it is the UCPD1_CC1 pad, "
     "which gets a 5.1 kohm pull-down while PB5 (SPI1_MOSI, floating in reset) is high (PROVISIONAL)"),
    # ---- IMU on SPI2: pads 34-36 at the corner next to the IMU, chip select and interrupts on the left edge
    ("SPI2_SCK", "PB13", "SPI2_SCK", "AF", "SPI2_SCK", 5, "none", "low", P, None, ""),
    ("SPI2_MOSI", "PB15", "SPI2_MOSI", "AF", "SPI2_MOSI", 5, "none", "low", P, None, ""),
    ("SPI2_MISO", "PB14", "SPI2_MISO", "AF", "SPI2_MISO", 5, "none", "input", P, None, ""),
    ("IMU_CS", "PB1", "IMU_CS", "OUT_PP", "GPIO", None, "none / 100k to V2V8", "high (not selected)", C, "PB12",
     "PB12 is the ROM bootloader's SPI2 chip-select input and PB14 its SPI2 data output, wired to the IMU's SDO. "
     "If the ROM enables a pull-down on PB12 (the remembered AN2606 text says it does), the 100k pull-up loses, "
     "the IMU is selected and its SDO fights PB14. On PB1 (left edge, next to the IMU, no bootloader function) "
     "the pull-up always wins and SDO stays high-impedance"),
    ("IMU_INT1", "PA7", "IMU_INT1", "EXTI", "GPIO (PWR_WKUP8)", None, "none", "input", C, "PC13",
     "PA7 faces the IMU and is a wake-up pin (WKUP8); PC13 is on the far corner next to the crystal and takes "
     "VBUS_SENSE"),
    ("IMU_INT2", "PA5", "IMU_INT2", "EXTI", "GPIO", None, "none", "input", C, "PC5",
     "PA5 faces the IMU. PA5 / PA7 are the ROM bootloader's SPI1 clock and data inputs: with both driven by the "
     "IMU they always have a defined level; PC5 takes NTC_BIAS"),
    # ---- grain sensor: the corner of the package next to the LED ring ------------------------
    ("GRAIN_CP0", "PA9", "CP0_MCU", "OUT_PP", "GPIO", None, "none / 68R series", "analog (no LED lit)", C, "PC0",
     "PC0-PC3 face the cameras and carry SCCB / PWDN now; PA9, PC10, PC12, PD2 are the corner next to the "
     "LED ring"),
    ("GRAIN_CP1", "PB0", "CP1_MCU", "OUT_PP", "GPIO", None, "none / 68R series", "analog (no LED lit)", C, "PC1",
     "PC1 carries SCCB data now. The free pad at the LED corner, PA15, is the UCPD1_CC1 pad (PINDATA): a 5.1 kohm "
     "dead-battery pull-down appears on it while PB5 is high until firmware sets UCPD_DBDIS, and its output "
     "stage may be weaker than an ordinary pad's (ST's FT_c structure; both PROVISIONAL, DS13086 not read). "
     "Line 1 lights 8 of the 16 LEDs at 5 to 10 mA, so it sits on an ordinary pad instead: PB0, the nearest "
     "one with no ROM bootloader function, exchanged with CHG_STAT"),
    ("GRAIN_CP2", "PC12", "CP2_MCU", "OUT_PP", "GPIO", None, "none / 68R series", "analog (no LED lit)", C, "PC2",
     "see GRAIN_CP0"),
    ("GRAIN_CP3", "PD2", "CP3_MCU", "OUT_PP", "GPIO", None, "none / 68R series", "analog (no LED lit)", C, "PC3",
     "see GRAIN_CP0"),
    ("GRAIN_CP4", "PC10", "CP4_MCU", "OUT_PP", "GPIO", None, "none / 68R series", "analog (no LED lit)", P, None, ""),
    ("OPAMP_VINP", "PA0", "VBIAS", "ANALOG", "OPAMP1_VINP", None, "none", "analog", S, None, ""),
    ("OPAMP_VINM", "PA1", "PD_K", "ANALOG", "OPAMP1_VINM", None, "none", "analog", S, None, ""),
    ("OPAMP_VOUT", "PA3", "OPAMP_OUT", "ANALOG", "OPAMP1_VOUT / ADC1_IN8", None, "none / 150k to V2V8", "analog", S, None, ""),
    # ---- power supervision -------------------------------------------------------------------
    ("VBAT_SENSE", "PA2", "VBAT_SENSE", "ANALOG", "ADC1_IN7", None, "none", "analog", P, None, ""),
    # E1: the charger's open-drain CHG output replaces the MCP73831 STAT of gl_pins.h
    ("CHG_STAT", "PA15", "CHG_STAT", "EXTI", "GPIO", None, "none / 100k to V2V8", "input", C, "PB0",
     "exchanged with GRAIN_CP1 (see there). An INPUT is what the UCPD1_CC1 pad can carry whatever its output "
     "stage is: its reset state (JTDI, internal pull-up) agrees with the 100 kohm pull-up, and a dead-battery "
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
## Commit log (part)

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2026-04-09 Add hotel revenue management system with demand forecasting, dynamic pricing, and EBITDA optimization
    Complete system for independent hotels to optimize RevPAR through rate-driven strategies while
    maximizing EBITDA. Includes demand forecasting (decomposition + pickup model), dynamic pricing
    engine with configurable aggressiveness and rate protection, EBITDA optimizer using scipy,
    displacement analysis for group bookings, PMS integration adapters (Cloudbeds/Opera/Mews),
    web dashboard with Jinja2+HTMX+Chart.js, and seed data script with 1 year of realistic
    reservation history for a 150-room boutique hotel.
